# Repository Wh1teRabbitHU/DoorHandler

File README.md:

# DoorHandler
This is a door handler/extender electronic project to monitor (almost) any type of door bells using a light sensor, a transmitter and a receiver module. The light sensor periodically checks the door phone if the signal is lit or not and sends a pulse to the receiver, which can be anywhere in the house and can provide visual and/or auditory signals to the home owners.

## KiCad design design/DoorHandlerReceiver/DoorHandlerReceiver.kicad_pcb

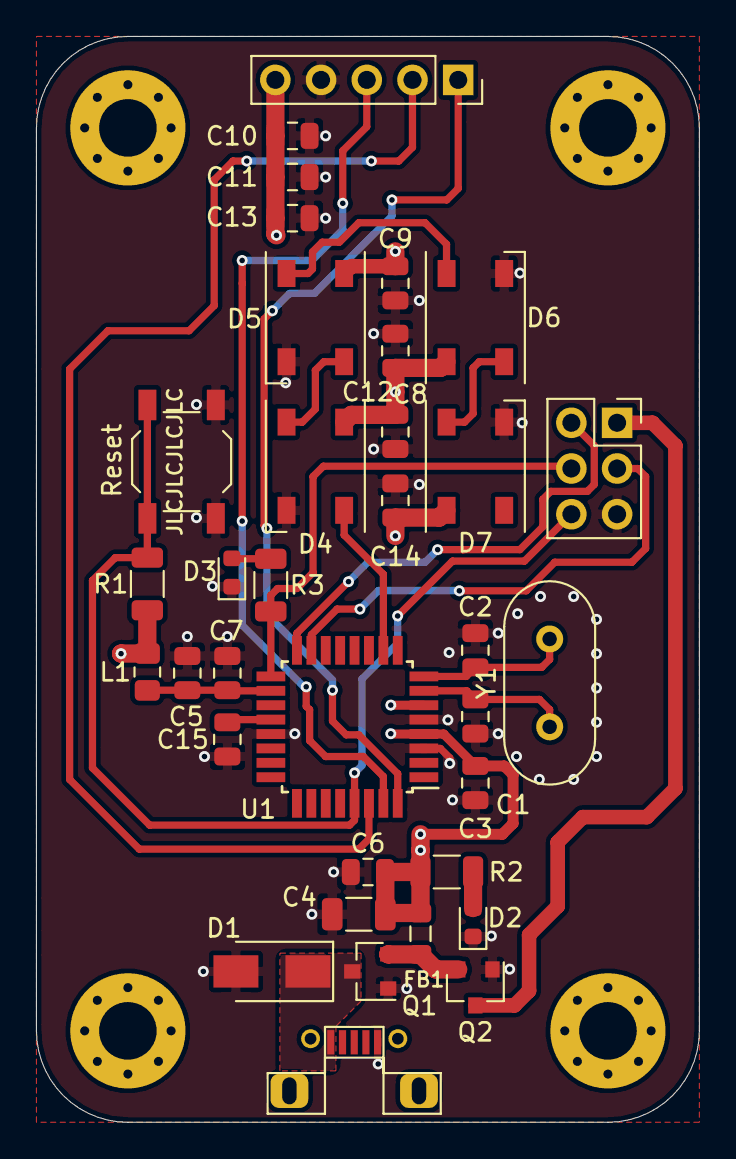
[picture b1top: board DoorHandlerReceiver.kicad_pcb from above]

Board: 4 copper layers, 36.8 x 60.3 mm, 39 parts (0 on the bottom side), 22 nets.

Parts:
C1, C2: 20pF; C_0805_2012Metric
C3, C6, C7, C8, C9, C12, C14, C15: 0.1uF; C_0805_2012Metric
C4: 10uF; C_1206_3216Metric
C5: 1uF; C_0805_2012Metric
C10, C11, C13: 22uF; C_0805_2012Metric
D1: TVS 5V 824501500; D_SMA
D2: Power LED; LED_0603_1608Metric
D3: Status LED; LED_0603_1608Metric
D4, D5, D6, D7: WS2812C; LED_WS2812B_PLCC4_5.0x5.0mm_P3.2mm
FB1: 100 FB; L_0805_2012Metric_Pad1.05x1.20mm_HandSolder
H1, H2, H3, H4: MountingHole; MountingHole_3.2mm_M3_Pad_Via
J1: USB_B_Micro_Without_Shield; Micro_USB_B_Female
J2: Conn_02x03_Odd_Even; PinSocket_2x03_P2.54mm_Vertical
J3: HC-12 Connector; PinSocket_1x05_P2.54mm_Vertical
L1: 39nH; L_0805_2012Metric_Pad1.15x1.40mm_HandSolder
Q1, Q2: AO3401A; SOT-23
R1: 10k; R_1206_3216Metric
R2, R3: 1.5k; R_1206_3216Metric
SW1: Reset button; SW_SPST_TL3342
U1: ATmega328P-AU; TQFP-32_7x7mm_P0.8mm
Y1: 16Mhz Crystal; Crystal_HC49-U_Vertical

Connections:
!RESET: J2.6, R1.2, SW1.1, U1.29
+5V: C3.1, C4.1, C6.1, C8.1, C9.1, C10.1, C11.1, C12.1, C13.1, C14.1, D4.1, D5.1, D6.1, D7.1, FB1.1, J3.5, L1.1, R1.1, R2.2, U1.4, U1.6
+5VA: C5.1, C7.1, L1.2, U1.18
AREF: C15.1, U1.20
D0: J3.2, U1.30
D1: J3.3, U1.31
D2: J3.1, U1.32
D6: D4.4, U1.10
D11: J2.3, U1.15
D12: J2.2, U1.16
D13: J2.4, R3.2, U1.17
GND: C1.2, C2.2, C3.2, C4.2, C5.2, C6.2, C7.2, C8.2, C9.2, C10.2, C11.2, C12.2, C13.2, C14.2, C15.2, D1.2, D2.1, D3.1, D4.3, D5.3, D6.3, D7.3, J1.5, J2.5, J3.4, Q1.1, Q2.1, SW1.2, U1.3, U1.5, U1.21
unnamed: D1.1, J1.1, Q1.3
unnamed: D2.2, R2.1
unnamed: D3.2, R3.1
unnamed: D4.2, D5.4
unnamed: D5.2, D6.4
unnamed: D6.2, D7.4
unnamed: FB1.2, Q1.2, Q2.2
VCC: J2.1, Q2.3
XTAL1: C1.1, U1.7, Y1.1
XTAL2: C2.1, U1.8, Y1.2

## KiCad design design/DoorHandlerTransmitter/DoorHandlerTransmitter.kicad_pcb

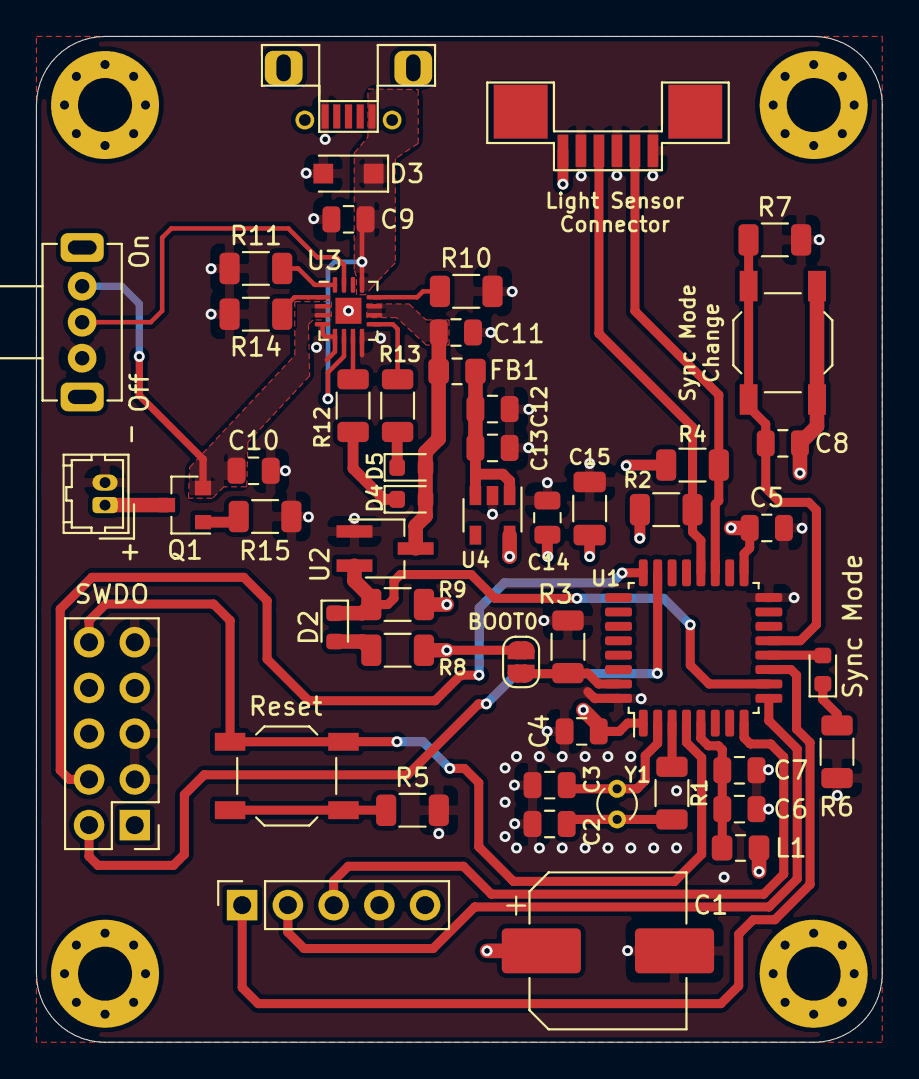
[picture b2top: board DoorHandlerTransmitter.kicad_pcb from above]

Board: 4 copper layers, 47.0 x 55.9 mm, 56 parts (0 on the bottom side), 35 nets.

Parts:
C1: 220uF; CP_Elec_8x10.5
C2, C3: 12pF; C_0805_2012Metric
C4, C5, C7, C8, C13, C14: 0.1uF; C_0805_2012Metric
C6, C9: 1uF; C_0805_2012Metric
C10, C11, C12: 4.7uF; C_0805_2012Metric
C15: 10uF; C_1206_3216Metric
D1: SYNC_STATE_LED; LED_0603_1608Metric
D2: Power Alert; LED_0603_1608Metric
D3: SMF6.0A; D_SOD-123F
D4: Input Good; LED_0603_1608Metric
D5: Charging; LED_0603_1608Metric
FB1: Ferrite_Bead; L_0805_2012Metric_Pad1.15x1.40mm_HandSolder
H1, H2, H3, H4: MountingHole; MountingHole_3mm_Pad_Via
J1: HC-12 Connector; PinSocket_1x05_P2.54mm_Vertical
J2: Light Sensor Connector; AFA07-S06FCA-00
J3: SWD; PinHeader_2x05_P2.54mm_Vertical
J4: USB_B_Micro_Without_Shield; Micro_USB_B_Female
J5: Battery Terminal; Hirose_DF13-02P-1.25DSA_1x02_P1.25mm_Vertical
JP1: BOOT0 JP; SolderJumper-2_P1.3mm_Open_RoundedPad1.0x1.5mm
L1: 39nH; L_0805_2012Metric_Pad1.15x1.40mm_HandSolder
Q1: AO3401A; SOT-23
R1: 100; R_1206_3216Metric
R2, R4: 2.2K; R_1206_3216Metric
R3, R5, R7: 10k; R_1206_3216Metric
R6, R8: 1.5k; R_1206_3216Metric
R9: 100k; R_1206_3216Metric
R10, R14, R15: 10K; R_1206_3216Metric
R11, R12, R13: 1K; R_1206_3216Metric
SW1: Reset Button; SW_SPST_TL3342
SW2: Sync Time Button; SW_SPST_TL3342
SW3: Enable; Toggle-Switch-SK12D07VG4
U1: STM32L031K6Tx; LQFP-32_7x7mm_P0.8mm
U2: APX803L05-36SA-7; SOT-23W_Handsoldering
U3: BQ24078RGTR; VQFN-16-1EP_3x3mm_P0.5mm_EP1.45x1.45mm
U4: ME6211C33M5G-N; SOT-23-5
Y1: 32.768kHz; Crystal_Round_D1.5mm_Vertical

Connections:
+3.3VA: C6.1, C7.1, L1.1, U1.5
+3V3: C1.1, C4.1, C5.1, C8.1, C14.1, C15.1, J1.5, J2.6, J3.1, JP1.2, L1.2, R2.1, R4.1, R8.1, R9.1, SW2.2, U1.1, U1.17, U4.5
/HC12_RX: J1.3, U1.8
/HC12_SET: J1.1, U1.11
/HC12_TX: J1.2, U1.9
/I2C_SCL: J2.2, R4.2, U1.19
/I2C_SDA: J2.4, R2.2, U1.20
/PWR_STATE: D2.1, R9.2, U1.10, U2.2
/Power Input/BAT+: C10.1, Q1.2, SW3.1, U3.2, U3.3
/Power Input/PWR_IN: C11.1, D4.2, D5.2, FB1.2, U2.3, U3.10, U3.11
/STM32/BOOT0: JP1.1, R3.1, U1.31
/STM32/PA6: D1.2, U1.12
/STM32/PA7: C8.2, R7.1, SW2.1, U1.13
/STM32/RESET: J3.10, SW1.1, U1.4
/STM32/SWCLK: J3.4, U1.24
/STM32/SWDIO: J3.2, U1.23
GND: C1.2, C2.2, C3.2, C4.2, C5.2, C6.2, C7.2, C9.2, C10.2, C11.2, C12.2, C13.2, C14.2, C15.2, D3.2, J1.4, J2.1, J2.3, J2.5, J3.3, J3.5, J3.9, J4.5, J5.2, R3.2, R5.2, R6.2, R7.2, R10.1, R11.1, R14.2, R15.2, SW3.3, U1.16, U1.32, U2.1, U3.4, U3.5, U3.8, U3.17, U4.2
unnamed: C2.1, R1.2, Y1.1
unnamed: C3.1, U1.2, Y1.2
unnamed: C9.1, D3.1, J4.1, U3.6, U3.13
unnamed: C12.1, C13.1, FB1.1, U4.1, U4.3
unnamed: D1.1, R6.1
unnamed: D2.2, R8.2
unnamed: D4.1, R12.1
unnamed: D5.1, R13.1
unnamed: J5.1, Q1.3
unnamed: Q1.1, R15.1
unnamed: R1.1, U1.3
unnamed: R5.1, SW1.2
unnamed: R10.2, U3.12
unnamed: R11.2, U3.16
unnamed: R12.2, U3.7
unnamed: R13.2, U3.9
unnamed: R14.1, U3.1
unnamed: SW3.2, U3.15

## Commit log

2022-03-19 Initial code for the transmitter
2022-03-19 Adding DoorHandlerTransmitter PCB design
2022-03-19 Adding DoorHandlerLightSensor PCB design
2022-03-19 Adding DoorHandlerReceiver PCB design
2022-03-26 Working communication
